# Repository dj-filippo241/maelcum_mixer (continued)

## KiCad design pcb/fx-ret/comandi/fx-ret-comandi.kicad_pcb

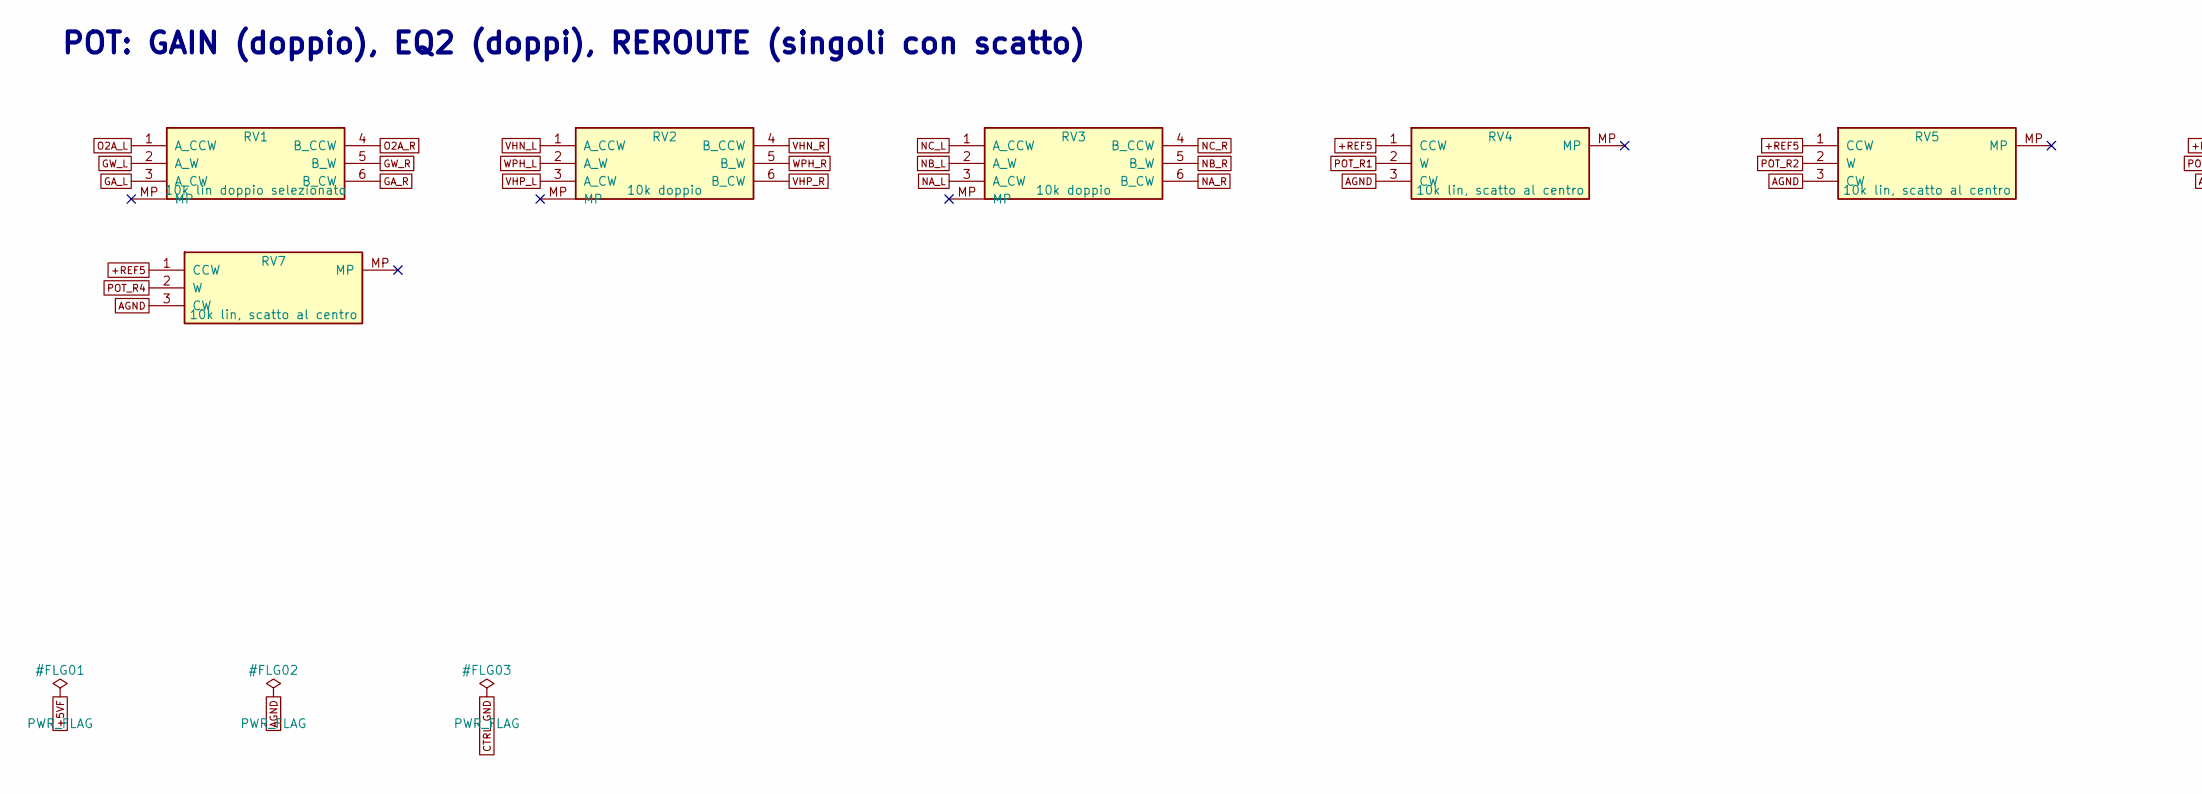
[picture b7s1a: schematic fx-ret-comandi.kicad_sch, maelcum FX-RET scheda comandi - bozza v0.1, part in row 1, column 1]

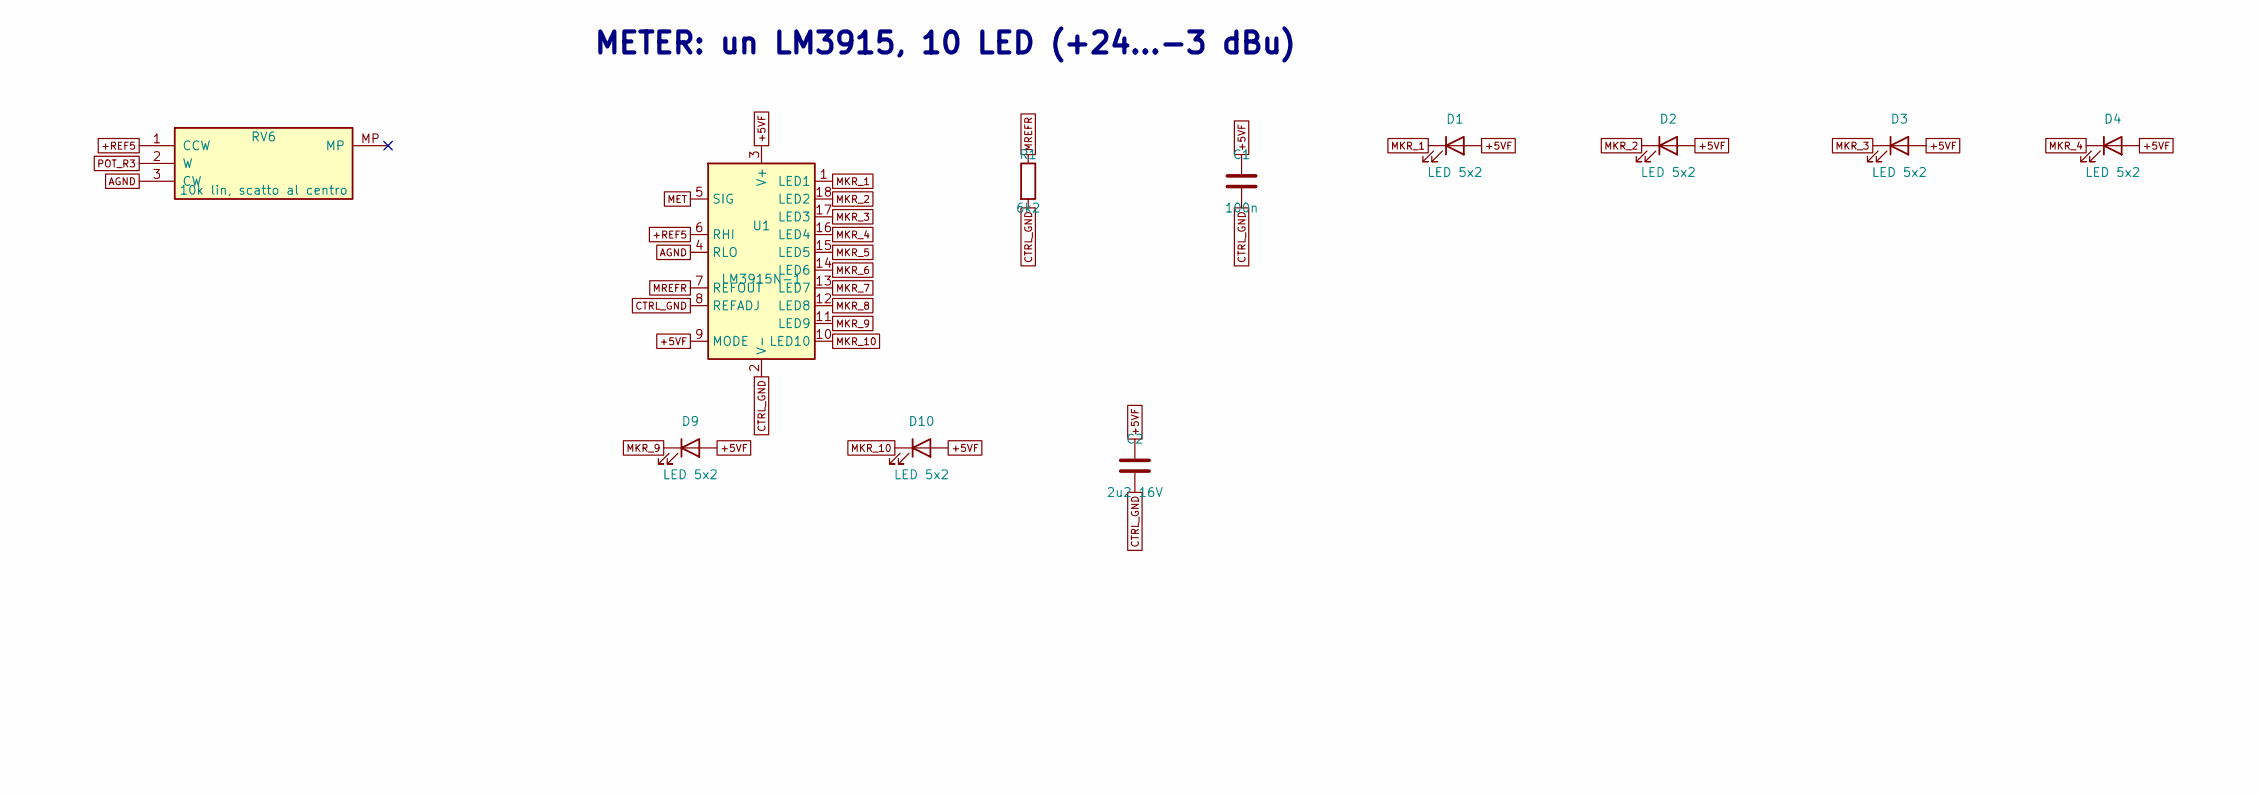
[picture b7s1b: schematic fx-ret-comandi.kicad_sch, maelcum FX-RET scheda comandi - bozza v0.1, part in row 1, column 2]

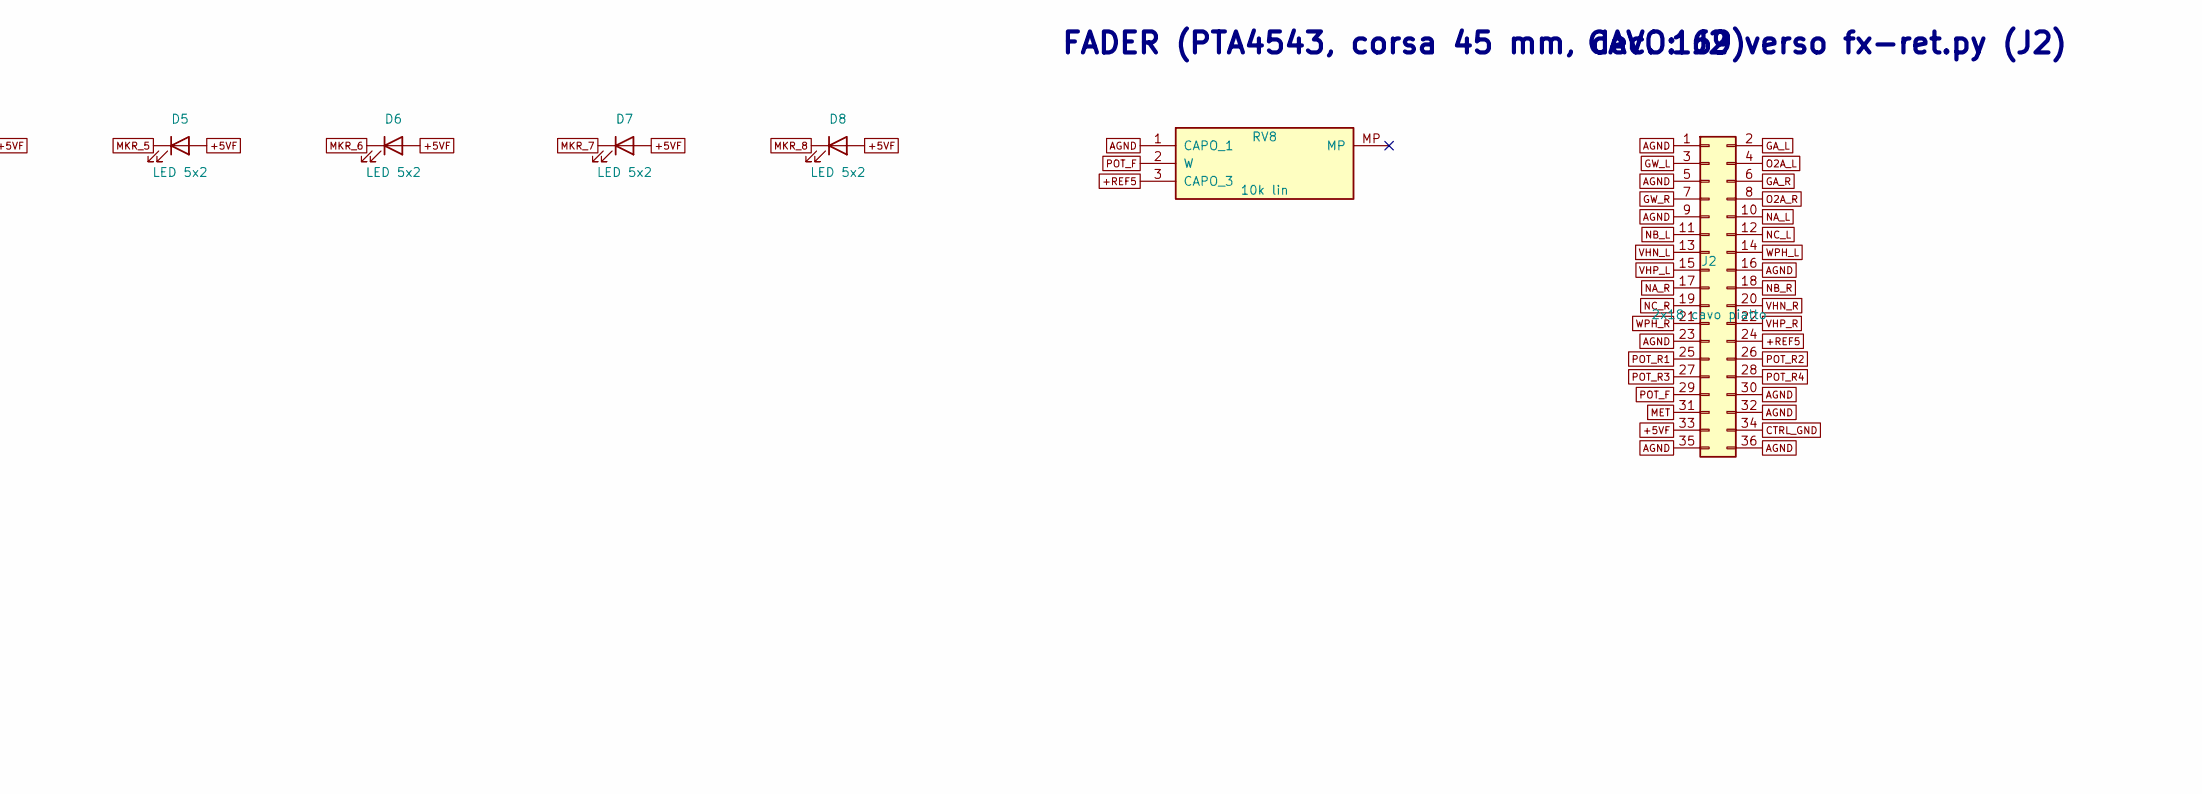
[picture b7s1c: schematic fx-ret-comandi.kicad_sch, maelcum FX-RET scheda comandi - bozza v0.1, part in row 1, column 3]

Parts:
C1: 100n; C_0805_2012Metric
C2: 2u2 16V; C_1206_3216Metric
D1, D2, D3, D4, D5, D6, D7, D8, D9, D10: LED 5x2; LED_Rectangular_W5.0mm_H2.0mm
J2: 2x18 cavo piatto; PinHeader_2x18_P2.54mm_Vertical
R1: 6k2; R_0805_2012Metric
RV1: 10k lin doppio selezionato; Potentiometer_Alps_RK09L_Double_Vertical
RV2, RV3: 10k doppio; Potentiometer_Alps_RK09L_Double_Vertical
RV4, RV5, RV6, RV7: 10k lin, scatto al centro; Potentiometer_Alps_RK09L_Single_Vertical
RV8: 10k lin; Potentiometer_Bourns_PTA4543_Single_Slide
U1: LM3915N-1; DIP-18_W7.62mm

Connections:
+5VF: C1.1, C2.1, D1.2 (A), D2.2 (A), D3.2 (A), D4.2 (A), D5.2 (A), D6.2 (A), D7.2 (A), D8.2 (A), D9.2 (A), D10.2 (A), J2.33, U1.3 (V+), U1.9 (MODE)
+REF5: J2.24, RV4.1 (CCW), RV5.1 (CCW), RV6.1 (CCW), RV7.1 (CCW), RV8.3 (CAPO_3), U1.6 (RHI)
AGND: J2.1, J2.5, J2.9, J2.16, J2.23, J2.30, J2.32, J2.35, J2.36, RV4.3 (CW), RV5.3 (CW), RV6.3 (CW), RV7.3 (CW), RV8.1 (CAPO_1), U1.4 (RLO)
CTRL_GND: C1.2, C2.2, J2.34, R1.2, U1.2 (V-), U1.8 (REFADJ)
GA_L: J2.2, RV1.3 (A_CW)
GA_R: J2.6, RV1.6 (B_CW)
GW_L: J2.3, RV1.2 (A_W)
GW_R: J2.7, RV1.5 (B_W)
MET: J2.31, U1.5 (SIG)
MKR_1: D1.1 (K), U1.1 (LED1)
MKR_2: D2.1 (K), U1.18 (LED2)
MKR_3: D3.1 (K), U1.17 (LED3)
MKR_4: D4.1 (K), U1.16 (LED4)
MKR_5: D5.1 (K), U1.15 (LED5)
MKR_6: D6.1 (K), U1.14 (LED6)
MKR_7: D7.1 (K), U1.13 (LED7)
MKR_8: D8.1 (K), U1.12 (LED8)
MKR_9: D9.1 (K), U1.11 (LED9)
MKR_10: D10.1 (K), U1.10 (LED10)
MREFR: R1.1, U1.7 (REFOUT)
NA_L: J2.10, RV3.3 (A_CW)
NA_R: J2.17, RV3.6 (B_CW)
NB_L: J2.11, RV3.2 (A_W)
NB_R: J2.18, RV3.5 (B_W)
NC_L: J2.12, RV3.1 (A_CCW)
NC_R: J2.19, RV3.4 (B_CCW)
O2A_L: J2.4, RV1.1 (A_CCW)
O2A_R: J2.8, RV1.4 (B_CCW)
POT_F: J2.29, RV8.2 (W)
POT_R1: J2.25, RV4.2 (W)
POT_R2: J2.26, RV5.2 (W)
POT_R3: J2.27, RV6.2 (W)
POT_R4: J2.28, RV7.2 (W)
VHN_L: J2.13, RV2.1 (A_CCW)
VHN_R: J2.20, RV2.4 (B_CCW)
VHP_L: J2.15, RV2.3 (A_CW)
VHP_R: J2.22, RV2.6 (B_CW)
WPH_L: J2.14, RV2.2 (A_W)
WPH_R: J2.21, RV2.5 (B_W)

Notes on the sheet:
POT: GAIN (doppio), EQ2 (doppi), REROUTE (singoli con scatto)
METER: un LM3915, 10 LED (+24...-3 dBu)
FADER (PTA4543, corsa 45 mm, dec. 169)
CAVO: J2 verso fx-ret.py (J2)

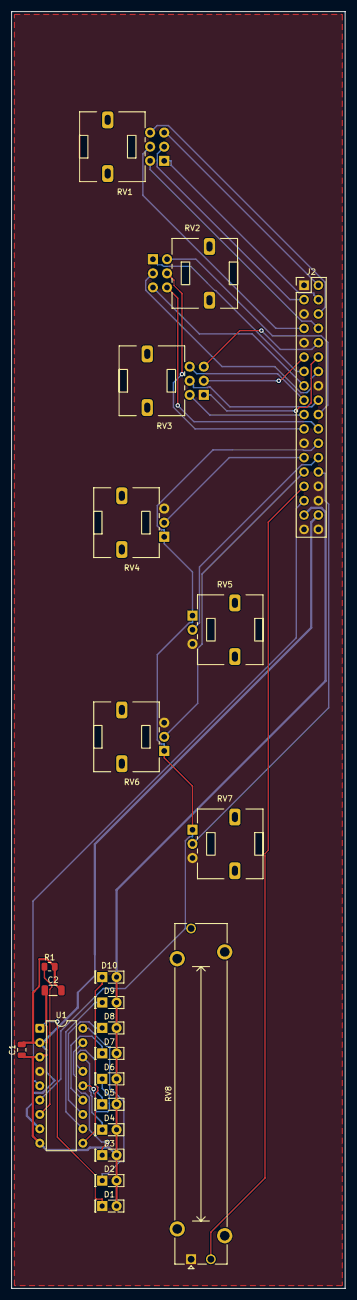
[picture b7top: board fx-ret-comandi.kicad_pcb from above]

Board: 4 copper layers, 59.0 x 225.9 mm, 23 parts (0 on the bottom side), 39 nets.

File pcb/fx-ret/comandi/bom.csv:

quantita;valore;impronta;riferimenti;nota
1;100n;C_0805_2012Metric;C1;disaccoppiamento dell'LM3915 R
1;2u2 16V;C_1206_3216Metric;C2;NOTA: riserva locale dei LED (cavo lungo)
1;LED 5x2;LED_Rectangular_W5.0mm_H2.0mm;D1;barra METER, segmento 1 di 10 (1 = soglia più bassa); colore: metering §3
1;LED 5x2;LED_Rectangular_W5.0mm_H2.0mm;D10;barra METER, segmento 10 di 10 (1 = soglia più bassa); colore: metering §3
1;LED 5x2;LED_Rectangular_W5.0mm_H2.0mm;D2;barra METER, segmento 2 di 10 (1 = soglia più bassa); colore: metering §3
1;LED 5x2;LED_Rectangular_W5.0mm_H2.0mm;D3;barra METER, segmento 3 di 10 (1 = soglia più bassa); colore: metering §3
1;LED 5x2;LED_Rectangular_W5.0mm_H2.0mm;D4;barra METER, segmento 4 di 10 (1 = soglia più bassa); colore: metering §3
1;LED 5x2;LED_Rectangular_W5.0mm_H2.0mm;D5;barra METER, segmento 5 di 10 (1 = soglia più bassa); colore: metering §3
1;LED 5x2;LED_Rectangular_W5.0mm_H2.0mm;D6;barra METER, segmento 6 di 10 (1 = soglia più bassa); colore: metering §3
1;LED 5x2;LED_Rectangular_W5.0mm_H2.0mm;D7;barra METER, segmento 7 di 10 (1 = soglia più bassa); colore: metering §3
1;LED 5x2;LED_Rectangular_W5.0mm_H2.0mm;D8;barra METER, segmento 8 di 10 (1 = soglia più bassa); colore: metering §3
1;LED 5x2;LED_Rectangular_W5.0mm_H2.0mm;D9;barra METER, segmento 9 di 10 (1 = soglia più bassa); colore: metering §3
1;2x18 cavo piatto;PinHeader_2x18_P2.54mm_Vertical;J2;stesso ordine di J2 su fx-ret.py
1;6k2;R_0805_2012Metric;R1;NOTA: corrente dei LED ~2 mA (metering §1): I = 12,5 V / R, formula del datasheet LM3915 da verificare
1;10k lin doppio selezionato;Potentiometer_Alps_RK09L_Double_Vertical;RV1;GAIN T2 (dec. 162): antiorario = silenzio; pot selezionato per il tracking L/R; manopola GAIN, pot di classe 14 mm, cappuccio 15.0 mm
1;10k doppio;Potentiometer_Alps_RK09L_Double_Vertical;RV2;EQ HIGH: tutto antiorario = kill (come il FX-SEND); manopola EQ HIGH, pot di classe 9 mm, cappuccio 11.0 mm
1;10k doppio;Potentiometer_Alps_RK09L_Double_Vertical;RV3;EQ LOW Baxandall: tutto antiorario = kill, cursore = massa virtuale; manopola EQ LOW, pot di classe 9 mm, cappuccio 11.0 mm
1;10k lin, scatto al centro;Potentiometer_Alps_RK09L_Single_Vertical;RV4;REROUTE 1 verso il bus S1 (SELF sul ritorno FX1, SELF sul ritorno FX1); manopola rovescia: antiorario = +REF5; manopola SELF, pot di classe 14 mm, cappuccio 12.0 mm
1;10k lin, scatto al centro;Potentiometer_Alps_RK09L_Single_Vertical;RV5;REROUTE 2 verso il bus S2 (> FX2 sul ritorno FX1, SELF sul ritorno FX2); manopola rovescia: antiorario = +REF5; manopola > FX2, pot di classe 14 mm, cappuccio 12.0 mm
1;10k lin, scatto al centro;Potentiometer_Alps_RK09L_Single_Vertical;RV6;REROUTE 3 verso il bus S3 (> FX3 sul ritorno FX1, SELF sul ritorno FX3); manopola rovescia: antiorario = +REF5; manopola > FX3, pot di classe 14 mm, cappuccio 12.0 mm
1;10k lin, scatto al centro;Potentiometer_Alps_RK09L_Single_Vertical;RV7;REROUTE 4 verso il bus S4 (> FX4 sul ritorno FX1, SELF sul ritorno FX4); manopola rovescia: antiorario = +REF5; manopola > FX4, pot di classe 14 mm, cappuccio 12.0 mm
1;10k lin;Potentiometer_Bourns_PTA4543_Single_Slide;RV8;FADER: in cima = 0 dB, in fondo = silenzio; fader FADER, corsa 45 mm (Bourns PTA4543, NOTA: pezzo da confermare)
1;LM3915N-1;DIP-18_W7.62mm;U1;barra METER, 10 segmenti da 3 dB sotto +REF5; modo barra (MODE a V+); V- a CTRL_GND: le correnti dei LED restano fuori da AGND

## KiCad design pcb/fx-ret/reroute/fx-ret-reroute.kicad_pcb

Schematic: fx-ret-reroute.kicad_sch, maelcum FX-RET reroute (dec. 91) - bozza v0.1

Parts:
C1, C2: 47u 25V; CP_Radial_D6.3mm_P2.50mm
C3, C4: 10u 25V; C_1206_3216Metric
C5, C6: 1u; C_1206_3216Metric
C7, C8, C10, C11, C13, C14, C16, C17, C18, C19, C21, C22, C24, C25, C27, C28, C29, C30, C32, C33, C35, C36, C38, C39, C40, C41, C43, C44, C46, C47, C49, C50, C51, C52, C53, C54: 100n; C_0805_2012Metric
C9, C12, C20, C23, C31, C34, C42, C45: 22p C0G; C_0805_2012Metric
C15, C26, C37, C48: 56n C0G; C_1210_3225Metric
D1, D2, D3, D4, D5, D6, D7, D8, D9, D10, D11, D12: 1N4148W; D_SOD-123
H1, H2, H3, H4: M3; MountingHole_3.2mm_M3
J1: 2x16 ponte reroute; PinHeader_2x16_P2.54mm_Vertical
R1, R5, R6, R10, R27, R31, R32, R36, R53, R57, R58, R62, R79, R83, R84, R88, R105, R106, R107, R108, R109, R110, R111, R112, R113, R114, R115, R116, R117, R118, R119, R120: 20k 0.1%; R_0805_2012Metric
R2, R7, R28, R33, R54, R59, R80, R85: 6k19; R_0805_2012Metric
R3, R8, R29, R34, R55, R60, R81, R86: 150k; R_0805_2012Metric
R4, R9, R30, R35, R56, R61, R82, R87: 51; R_0805_2012Metric
R11, R37, R63, R89: 37.4k 0.1%; R_0805_2012Metric
R12, R38, R64, R90: 43.2k 0.1%; R_0805_2012Metric
R13, R39, R65, R91: 1M 0.1%; R_0805_2012Metric
R14, R40, R66, R92: 18.7k 0.1%; R_0805_2012Metric
R15, R41, R67, R93: 40.2k 0.1%; R_0805_2012Metric
R16, R42, R68, R94: 2.61k 0.1%; R_0805_2012Metric
R17, R43, R69, R95: 3.83k 0.1%; R_0805_2012Metric
R18, R44, R70, R96: 10k 0.1%; R_0805_2012Metric
R19, R45, R71, R97: 9k76 0.1%; R_0805_2012Metric
R20, R46, R72, R98: 18k7 0.1%; R_0805_2012Metric
R21, R47, R73, R99: 100k; R_0805_2012Metric
R22, R48, R74, R100: 18k2 0.1%; R_0805_2012Metric
R23, R25, R49, R51, R75, R77, R101, R103: 1k 0.1%; R_0805_2012Metric
R24, R50, R76, R102: 17k4 0.1%; R_0805_2012Metric
R26, R52, R78, R104: 2M7; R_0805_2012Metric
RV1, RV2, RV4, RV5, RV6, RV8, RV9, RV10, RV12, RV13, RV14, RV16: 50k; Potentiometer_Bourns_3214W_Vertical
RV3, RV7, RV11, RV15: 2k; Potentiometer_Bourns_3214W_Vertical
U10, U11, U14, U15, U18, U19, U22, U23: V2181L; SOIC-8_3.9x4.9mm_P1.27mm
U12, U13, U16, U17, U20, U21, U24, U25: OPA1612AIDR; SOIC-8_3.9x4.9mm_P1.27mm
U26, U27: OPA1654AIDR; SOIC-14_3.9x8.7mm_P1.27mm

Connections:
+15LN: C3.1, C16.1, C27.1, C38.1, C49.1, J1.7, RV1.1, RV2.1, RV4.1, RV5.1, RV6.1, RV8.1, RV9.1, RV10.1, RV12.1, RV13.1, RV14.1, RV16.1, U13.8 (V+), U17.8 (V+), U21.8 (V+), U25.8 (V+)
+18V: C1.1, C7.1, C10.1, C13.1, C18.1, C21.1, C24.1, C29.1, C32.1, C35.1, C40.1, C43.1, C46.1, C51.1, C53.1, J1.1, J1.2, U10.7 (V+), U11.7 (V+), U12.8 (V+), U14.7 (V+), U15.7 (V+), U16.8 (V+), U18.7 (V+), U19.7 (V+), U20.8 (V+), U22.7 (V+), U23.7 (V+), U24.8 (V+), U26.4 (V+), U27.4 (V+)
+REF5: C5.1, J1.11
-15LN: C4.2, C17.2, C28.2, C39.2, C50.2, J1.8, RV1.3, RV2.3, RV4.3, RV5.3, RV6.3, RV8.3, RV9.3, RV10.3, RV12.3, RV13.3, RV14.3, RV16.3, U13.4 (V-), U17.4 (V-), U21.4 (V-), U25.4 (V-)
-18V: C2.2, C8.2, C11.2, C14.2, C19.2, C22.2, C25.2, C30.2, C33.2, C36.2, C41.2, C44.2, C47.2, C52.2, C54.2, J1.5, J1.6, R2.2, R7.2, R28.2, R33.2, R54.2, R59.2, R80.2, R85.2, U12.4 (V-), U16.4 (V-), U20.4 (V-), U24.4 (V-), U26.11 (V-), U27.11 (V-)
-REF5: C6.2, J1.12, R13.2, R15.2, R17.2, R39.2, R41.2, R43.2, R65.2, R67.2, R69.2, R91.2, R93.2, R95.2
AGND: C1.2, C2.1, C3.2, C4.1, C5.2, C6.1, C7.2, C8.1, C10.2, C11.1, C13.2, C14.1, C16.2, C17.1, C18.2, C19.1, C21.2, C22.1, C24.2, C25.1, C27.2, C28.1, C29.2, C30.1, C32.2, C33.1, C35.2, C36.1, C38.2, C39.1, C40.2, C41.1, C43.2, C44.1, C46.2, C47.1, C49.2, C50.1, C51.2, C52.1, C53.2, C54.1, J1.3, J1.4, J1.9, J1.10, J1.13, J1.14, J1.17, J1.18, J1.27, J1.28, R4.2, R9.2, R21.2, R23.2, R25.2, R30.2, R35.2, R47.2, R49.2, R51.2, R56.2, R61.2, R73.2, R75.2, R77.2, R82.2, R87.2, R99.2, R101.2, R103.2, U10.2 (EC+), U10.6 (GND), U11.2 (EC+), U11.6 (GND), U12.3 (+), U12.5 (+), U13.3 (+), U13.5 (+), U14.2 (EC+), U14.6 (GND), U15.2 (EC+), U15.6 (GND), U16.3 (+), U16.5 (+), U17.3 (+), U17.5 (+), U18.2 (EC+), U18.6 (GND), U19.2 (EC+), U19.6 (GND), U20.3 (+), U20.5 (+), U21.3 (+), U21.5 (+), U22.2 (EC+), U22.6 (GND), U23.2 (EC+), U23.6 (GND), U24.3 (+), U24.5 (+), U25.3 (+), U25.5 (+), U26.3 (+), U26.5 (+), U26.10 (+), U26.12 (+), U27.3 (+), U27.5 (+), U27.10 (+), U27.12 (+)
CVP_R1: C15.2, R20.2, R22.1, R24.1, U13.7
CVP_R2: C26.2, R46.2, R48.1, R50.1, U17.7
CVP_R3: C37.2, R72.2, R74.1, R76.1, U21.7
CVP_R4: C48.2, R98.2, R100.1, R102.1, U25.7
DIR1_L: J1.19, R106.2, U26.1
DIR1_R: J1.20, R108.2, U27.1
DIR2_L: J1.21, R110.2, U26.7
DIR2_R: J1.22, R112.2, U27.7
DIR3_L: J1.23, R114.2, U26.8
DIR3_R: J1.24, R116.2, U27.8
DIR4_L: J1.25, R118.2, U26.14
DIR4_R: J1.26, R120.2, U27.14
ECR1_L: R22.2, R23.1, U10.3 (EC-)
ECR1_R: R25.1, R26.2, RV3.2, RV3.3, U11.3 (EC-)
ECR2_L: R48.2, R49.1, U14.3 (EC-)
ECR2_R: R51.1, R52.2, RV7.2, RV7.3, U15.3 (EC-)
ECR3_L: R74.2, R75.1, U18.3 (EC-)
ECR3_R: R77.1, R78.2, RV11.2, RV11.3, U19.3 (EC-)
ECR4_L: R100.2, R101.1, U22.3 (EC-)
ECR4_R: R103.1, R104.2, RV15.2, RV15.3, U23.3 (EC-)
IVR1_L: C9.2, R5.2, R105.1, U12.1
IVR1_R: C12.2, R10.2, R107.1, U12.7
IVR2_L: C20.2, R31.2, R109.1, U16.1
IVR2_R: C23.2, R36.2, R111.1, U16.7
IVR3_L: C31.2, R57.2, R113.1, U20.1
IVR3_R: C34.2, R62.2, R115.1, U20.7
IVR4_L: C42.2, R83.2, R117.1, U24.1
IVR4_R: C45.2, R88.2, R119.1, U24.7
LT_R1: R24.2, RV3.1
LT_R2: R50.2, RV7.1
LT_R3: R76.2, RV11.1
LT_R4: R102.2, RV15.1
NDR1_L: R105.2, R106.1, U26.2 (-)
NDR1_R: R107.2, R108.1, U27.2 (-)
NDR2_L: R109.2, R110.1, U26.6 (-)
NDR2_R: R111.2, R112.1, U27.6 (-)
NDR3_L: R113.2, R114.1, U26.9 (-)
NDR3_R: R115.2, R116.1, U27.9 (-)
NDR4_L: R117.2, R118.1, U26.13 (-)
NDR4_R: R119.2, R120.1, U27.13 (-)
NIR1_L: C9.1, R5.1, U10.8 (OUT), U12.2 (-)
NIR1_R: C12.1, R10.1, U11.8 (OUT), U12.6 (-)
NIR2_L: C20.1, R31.1, U14.8 (OUT), U16.2 (-)
NIR2_R: C23.1, R36.1, U15.8 (OUT), U16.6 (-)
NIR3_L: C31.1, R57.1, U18.8 (OUT), U20.2 (-)
NIR3_R: C34.1, R62.1, U19.8 (OUT), U20.6 (-)
NIR4_L: C42.1, R83.1, U22.8 (OUT), U24.2 (-)
NIR4_R: C45.1, R88.1, U23.8 (OUT), U24.6 (-)
NP_R1: C15.1, R19.2, R20.1, U13.6 (-)
NP_R2: C26.1, R45.2, R46.1, U17.6 (-)
NP_R3: C37.1, R71.2, R72.1, U21.6 (-)
NP_R4: C48.1, R97.2, R98.1, U25.6 (-)
OF_R1: R26.1, RV4.2
OF_R2: R52.1, RV8.2
OF_R3: R78.1, RV12.2
OF_R4: R104.1, RV16.2
POT_R1: J1.29, R11.1, R12.1, R14.1, R16.1, R21.1
POT_R2: J1.30, R37.1, R38.1, R40.1, R42.1, R47.1
POT_R3: J1.31, R63.1, R64.1, R66.1, R68.1, R73.1
POT_R4: J1.32, R89.1, R90.1, R92.1, R94.1, R99.1
RRN_L: J1.15, R1.1, R27.1, R53.1, R79.1
RRN_R: J1.16, R6.1, R32.1, R58.1, R84.1
SH_R1: R18.2, R19.1, U13.1
SH_R2: R44.2, R45.1, U17.1
SH_R3: R70.2, R71.1, U21.1
SH_R4: R96.2, R97.1, U25.1
SJ_R1: D1.1 (K), D2.1 (K), D3.1 (K), R11.2, R18.1, U13.2 (-)
SJ_R2: D4.1 (K), D5.1 (K), D6.1 (K), R37.2, R44.1, U17.2 (-)
SJ_R3: D7.1 (K), D8.1 (K), D9.1 (K), R63.2, R70.1, U21.2 (-)
SJ_R4: D10.1 (K), D11.1 (K), D12.1 (K), R89.2, R96.1, U25.2 (-)
SN1_R1: D1.2 (A), R12.2, R13.1
SN1_R2: D4.2 (A), R38.2, R39.1
SN1_R3: D7.2 (A), R64.2, R65.1
SN1_R4: D10.2 (A), R90.2, R91.1
SN2_R1: D2.2 (A), R14.2, R15.1
SN2_R2: D5.2 (A), R40.2, R41.1
SN2_R3: D8.2 (A), R66.2, R67.1
SN2_R4: D11.2 (A), R92.2, R93.1
SN3_R1: D3.2 (A), R16.2, R17.1
SN3_R2: D6.2 (A), R42.2, R43.1
SN3_R3: D9.2 (A), R68.2, R69.1
SN3_R4: D12.2 (A), R94.2, R95.1
SW_r1l: R3.1, RV1.2
SW_r1r: R8.1, RV2.2
SW_r2l: R29.1, RV5.2
SW_r2r: R34.1, RV6.2
SW_r3l: R55.1, RV9.2
SW_r3r: R60.1, RV10.2
SW_r4l: R81.1, RV13.2
SW_r4r: R86.1, RV14.2
SYM_r1l: R3.2, R4.1, U10.4 (SYM)
SYM_r1r: R8.2, R9.1, U11.4 (SYM)
SYM_r2l: R29.2, R30.1, U14.4 (SYM)
SYM_r2r: R34.2, R35.1, U15.4 (SYM)
SYM_r3l: R55.2, R56.1, U18.4 (SYM)
SYM_r3r: R60.2, R61.1, U19.4 (SYM)
SYM_r4l: R81.2, R82.1, U22.4 (SYM)
SYM_r4r: R86.2, R87.1, U23.4 (SYM)
VEE_r1l: R2.1, U10.5 (V-)
VEE_r1r: R7.1, U11.5 (V-)
VEE_r2l: R28.1, U14.5 (V-)
VEE_r2r: R33.1, U15.5 (V-)
VEE_r3l: R54.1, U18.5 (V-)
VEE_r3r: R59.1, U19.5 (V-)
VEE_r4l: R80.1, U22.5 (V-)
VEE_r4r: R85.1, U23.5 (V-)
VIN_r1l: R1.2, U10.1 (IN)
VIN_r1r: R6.2, U11.1 (IN)
VIN_r2l: R27.2, U14.1 (IN)
VIN_r2r: R32.2, U15.1 (IN)
VIN_r3l: R53.2, U18.1 (IN)
VIN_r3r: R58.2, U19.1 (IN)
VIN_r4l: R79.2, U22.1 (IN)
VIN_r4r: R84.2, U23.1 (IN)

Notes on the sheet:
PONTE dalla scheda segnale (J1) e bulk locali
REROUTE verso S1 (2 VCA, I/V, driver invertente, shaper reroute, trim)
REROUTE verso S2 (2 VCA, I/V, driver invertente, shaper reroute, trim)
REROUTE verso S3 (2 VCA, I/V, driver invertente, shaper reroute, trim)
REROUTE verso S4 (2 VCA, I/V, driver invertente, shaper reroute, trim)
DRIVER D'INIEZIONE dei reroute (2 OPA1654, invertenti unity)

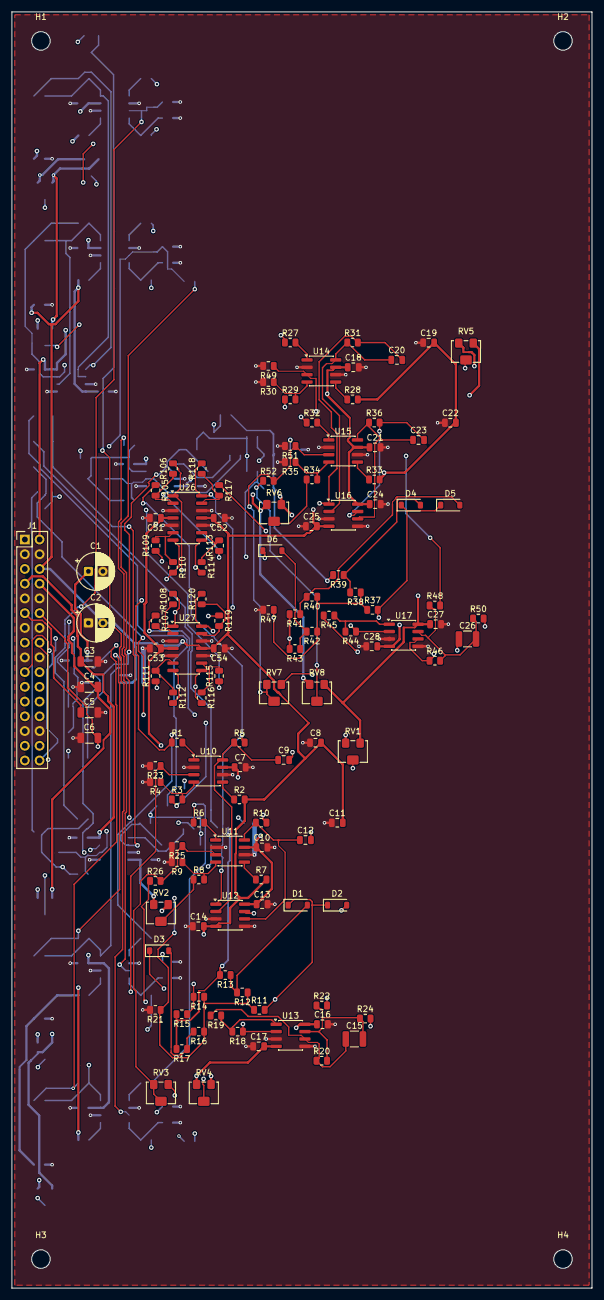
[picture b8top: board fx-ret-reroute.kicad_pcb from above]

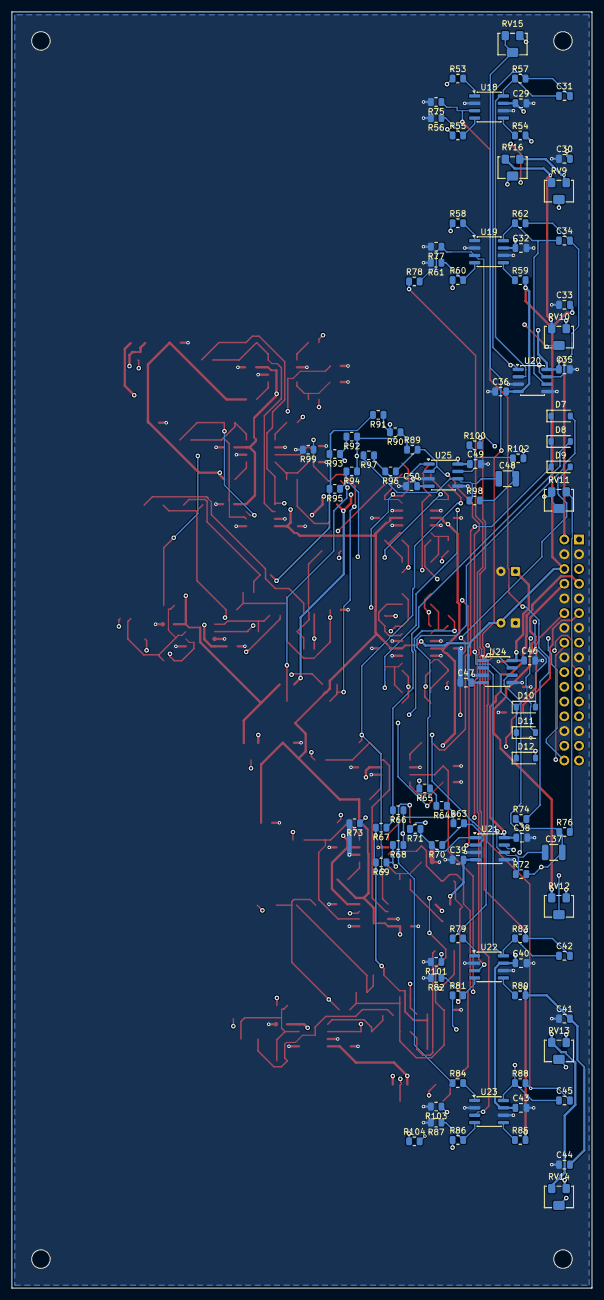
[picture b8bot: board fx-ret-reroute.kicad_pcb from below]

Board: 4 copper layers, 100.0 x 220.0 mm, 225 parts (96 on the bottom side), 121 nets.

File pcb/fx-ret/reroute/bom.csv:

quantita;valore;impronta;riferimenti;nota
2;47u 25V;CP_Radial_D6.3mm_P2.50mm;C1 C2;NOTA: bulk locale dopo il cavo
4;56n C0G;C_1210_3225Metric;C15 C26 C37 C48;NOTA: smoothing 1 ms (dec. 80) come C sulla Rf: 18,7k x 56n = 1,05 ms
2;10u 25V;C_1206_3216Metric;C3 C4;NOTA: locale dopo il cavo
2;1u;C_1206_3216Metric;C5 C6;NOTA: locale dopo il cavo
36;100n;C_0805_2012Metric;C7 C8 C10 C11 C13 C14 C16 C17 C18 C19 C21 C22 C24 C25 C27 C28 C29 C30 C32 C33 C35 C36 C38 C39 C40 C41 C43 C44 C46 C47 C49 C50 C51 C52 C53 C54;
8;22p C0G;C_0805_2012Metric;C9 C12 C20 C23 C31 C34 C42 C45;
12;1N4148W;D_SOD-123;D1 D2 D3 D4 D5 D6 D7 D8 D9 D10 D11 D12;
1;2x16 ponte reroute;PinHeader_2x16_P2.54mm_Vertical;J1;NOTA: cavo piatto 2x16 dalla scheda segnale (J4 di fx-ret.py)
24;20k 0.1%;R_0805_2012Metric;R1 R5 R6 R10 R27 R31 R32 R36 R53 R57 R58 R62 R79 R83 R84 R88 R105 R107 R109 R111 R113 R115 R117 R119;
8;20k 0.1%;R_0805_2012Metric;R106 R108 R110 R112 R114 R116 R118 R120;driver d'iniezione invertente (F3)
4;37.4k 0.1%;R_0805_2012Metric;R11 R37 R63 R89;
4;43.2k 0.1%;R_0805_2012Metric;R12 R38 R64 R90;
4;1M 0.1%;R_0805_2012Metric;R13 R39 R65 R91;
4;18.7k 0.1%;R_0805_2012Metric;R14 R40 R66 R92;
4;40.2k 0.1%;R_0805_2012Metric;R15 R41 R67 R93;
4;2.61k 0.1%;R_0805_2012Metric;R16 R42 R68 R94;
4;3.83k 0.1%;R_0805_2012Metric;R17 R43 R69 R95;
4;10k 0.1%;R_0805_2012Metric;R18 R44 R70 R96;
4;9k76 0.1%;R_0805_2012Metric;R19 R45 R71 R97;
8;6k19;R_0805_2012Metric;R2 R7 R28 R33 R54 R59 R80 R85;5,1k del datasheet a -15 V riscalato a -18 V (come il master)
4;18k7 0.1%;R_0805_2012Metric;R20 R46 R72 R98;stadio del partitore x(-1,916): CV al pin = out/10,02 (todo 281)
4;100k;R_0805_2012Metric;R21 R47 R73 R99;pot staccato = shaper a 0 V (come il master)
4;18k2 0.1%;R_0805_2012Metric;R22 R48 R74 R100;
8;1k 0.1%;R_0805_2012Metric;R23 R25 R49 R51 R75 R77 R101 R103;
4;17k4 0.1%;R_0805_2012Metric;R24 R50 R76 R102;
4;2M7;R_0805_2012Metric;R26 R52 R78 R104;partitore da ~950 ohm: 2,7M = +-5,3 mV come prima
8;150k;R_0805_2012Metric;R3 R8 R29 R34 R55 R60 R81 R86;
8;51;R_0805_2012Metric;R4 R9 R30 R35 R56 R61 R82 R87;
8;50k;Potentiometer_Bourns_3214W_Vertical;RV1 RV2 RV5 RV6 RV9 RV10 RV13 RV14;trim di simmetria (THD minima)
4;2k;Potentiometer_Bourns_3214W_Vertical;RV3 RV7 RV11 RV15;trim di law, 25 giri (vca-trim §3.2): montato solo se la coppia esce da 0,5 dB
4;50k;Potentiometer_Bourns_3214W_Vertical;RV4 RV8 RV12 RV16;trim d'offset di coppia
8;V2181L;SOIC-8_3.9x4.9mm_P1.27mm;U10 U11 U14 U15 U18 U19 U22 U23;
1;OPA1612AIDR;SOIC-8_3.9x4.9mm_P1.27mm;U12;I/V dei VCA del reroute 1
1;OPA1612AIDR;SOIC-8_3.9x4.9mm_P1.27mm;U13;shaper R1
1;OPA1612AIDR;SOIC-8_3.9x4.9mm_P1.27mm;U16;I/V dei VCA del reroute 2
1;OPA1612AIDR;SOIC-8_3.9x4.9mm_P1.27mm;U17;shaper R2
1;OPA1612AIDR;SOIC-8_3.9x4.9mm_P1.27mm;U20;I/V dei VCA del reroute 3
1;OPA1612AIDR;SOIC-8_3.9x4.9mm_P1.27mm;U21;shaper R3
1;OPA1612AIDR;SOIC-8_3.9x4.9mm_P1.27mm;U24;I/V dei VCA del reroute 4
1;OPA1612AIDR;SOIC-8_3.9x4.9mm_P1.27mm;U25;shaper R4
1;OPA1654AIDR;SOIC-14_3.9x8.7mm_P1.27mm;U26;reroute 1-4, lato L
1;OPA1654AIDR;SOIC-14_3.9x8.7mm_P1.27mm;U27;reroute 1-4, lato R
